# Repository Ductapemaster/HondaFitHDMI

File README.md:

# HondaFitHDMI
Various efforts into hacking the 2015 Honda Fit head unit to allow HDMI input and disable other lockouts while driving

A demonstration of the prototype hardware can be found here: http://youtu.be/ffWo1LNsV7A

Please see the Wiki for the most updated information!

## Contents
**./can_analysis**: Captured data from CAN bus.  Analysis spreadsheet showing various IDs and their functions

**./proof_of_concept**: Files relating to the proof of concept hardware and software

**./teensy**: Firmware and related information for teensy-based prototype hardware

**./wiki**: Wiki content

# Git-iquette
Please forgive my tresspasses on the typical Git workflow.  This is my first solo git-tracked project and I'm learning as I go along!

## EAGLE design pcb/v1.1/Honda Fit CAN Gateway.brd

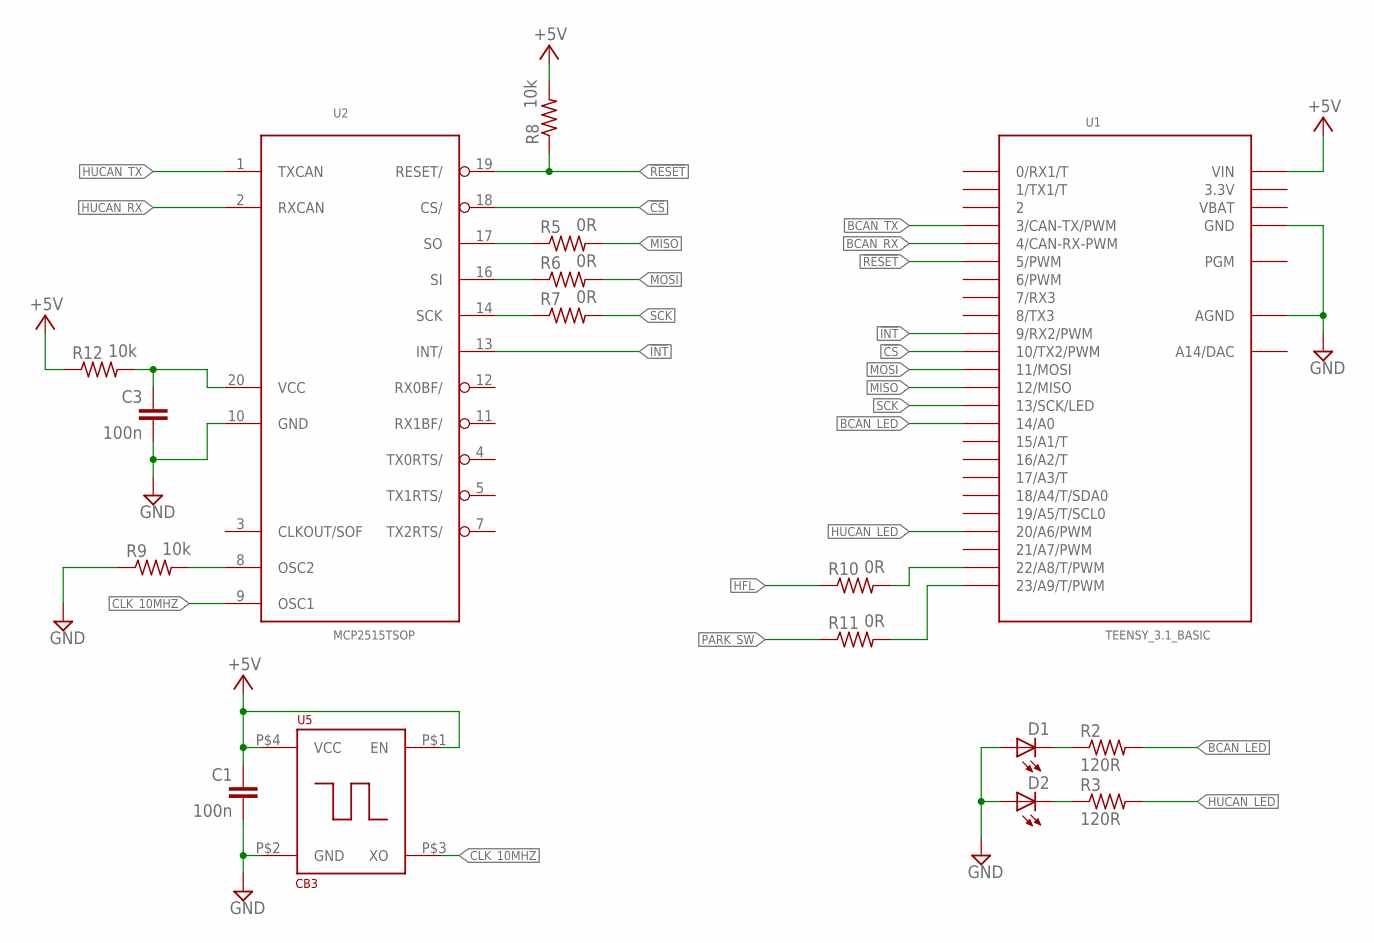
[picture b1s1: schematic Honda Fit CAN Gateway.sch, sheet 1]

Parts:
C1, C3: 100n; C0603
D1, D2: LEDCHIP-LED0805; CHIP-LED0805
R2, R3: 120R; R0805
R5, R6, R7, R10, R11: 0R; R0805
R8, R9, R12: 10k; R0805
U1: TEENSY_3.1_BASIC
U2: MCP2515TSOP; TSSOP20
U5: CB3; 4-SMD

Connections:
3.3V: U1.3.3V, U1.3.3V1 (3.3V)
!CS: U1.10 (10/TX2/PWM), U2.18 (CS/)
!INT: U1.9 (9/RX2/PWM), U2.13 (INT/)
!RESET: R8.1, U1.5 (5/PWM), U2.19 (RESET/)
+5V: C1.1, R8.2, R12.1, U1.VIN, U5.P$1 (EN), U5.P$4 (VCC); also elsewhere on the board
BCAN_LED: R2.2, U1.14/A0
BCAN_RX: U1.4 (4/CAN-RX-PWM); also elsewhere on the board
BCAN_TX: U1.3 (3/CAN-TX/PWM); also elsewhere on the board
CLK_10MHZ: U2.9 (OSC1), U5.P$3 (XO)
GND: C1.2, C3.2, D1.A, D2.A, R9.1, U1.AGND, U1.GND, U1.GND1 (GND), U2.10 (GND), U5.P$2 (GND); also elsewhere on the board
HFL: R10.1; also elsewhere on the board
HUCAN_LED: R3.2, U1.20/A6 (20/A6/PWM)
HUCAN_RX: U2.2 (RXCAN); also elsewhere on the board
HUCAN_TX: U2.1 (TXCAN); also elsewhere on the board
MISO: R5.2, U1.12 (12/MISO)
MOSI: R6.2, U1.11 (11/MOSI)
unnamed: R9.2, U2.8 (OSC2)
unnamed: R10.2, U1.22/A8 (22/A8/T/PWM)
unnamed: R11.2, U1.23/A9 (23/A9/T/PWM)
unnamed: D1.C, R2.1
unnamed: D2.C, R3.1
unnamed: R5.1, U2.17 (SO)
unnamed: R6.1, U2.16 (SI)
unnamed: R7.1, U2.14 (SCK)
unnamed: C3.1, R12.2, U2.20 (VCC)
PARK_SW: R11.1; also elsewhere on the board
SCK: R7.2, U1.13 (13/SCK/LED)
VBAT: U1.VBAT

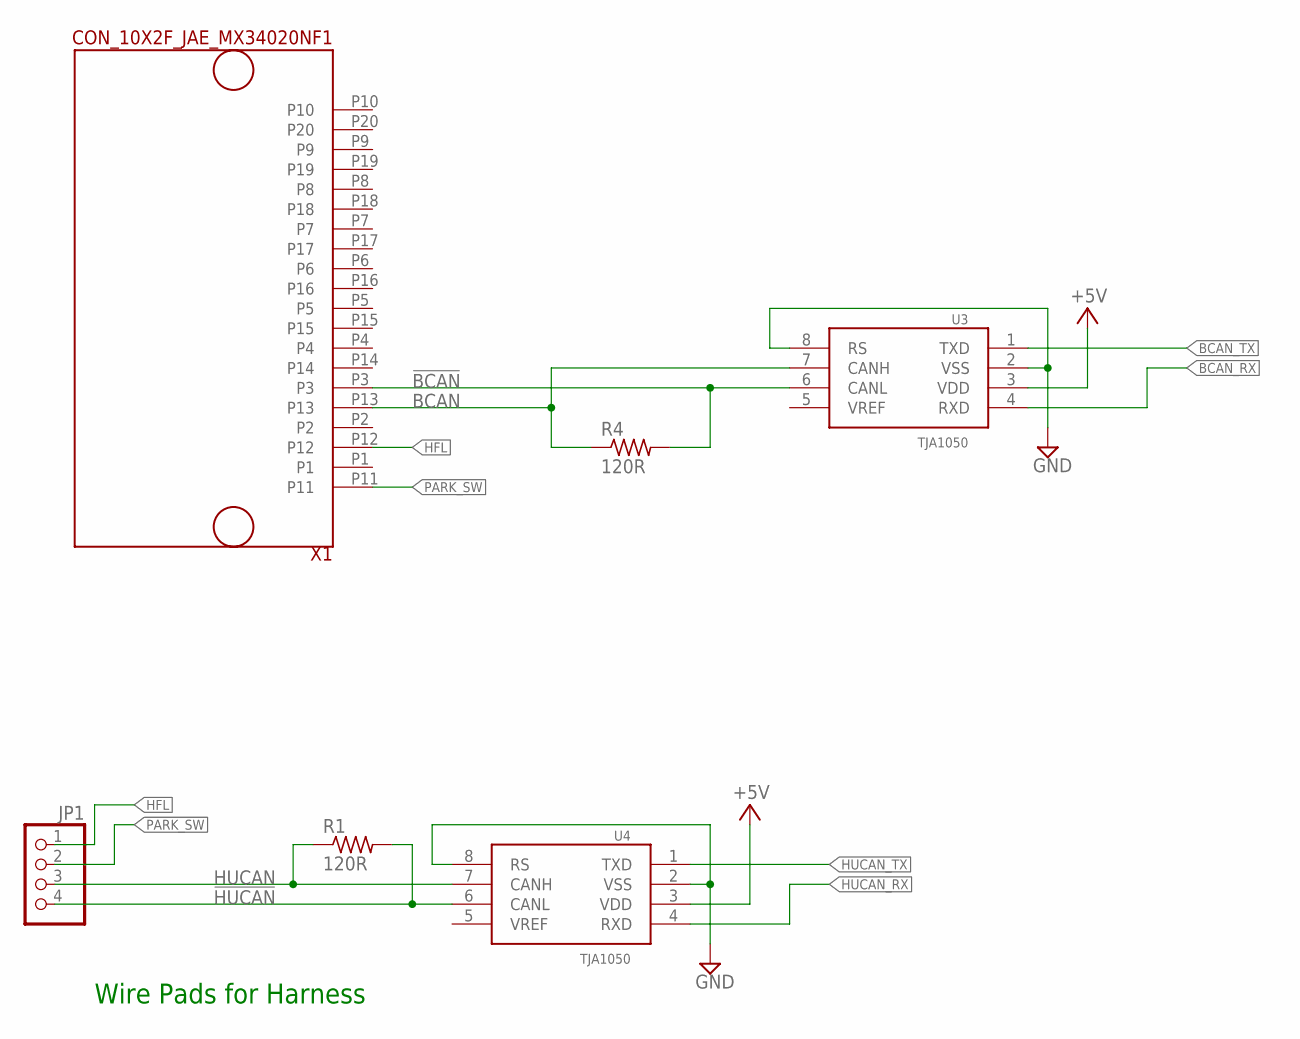
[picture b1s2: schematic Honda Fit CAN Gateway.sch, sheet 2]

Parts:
JP1: PINHD-1X4; 1X04
R1, R4: 120R; R0805
U3, U4: TJA1050; SO08
X1: CON_10X2F_JAE_MX34020NF1; CON_10X2_JAE_MX34020NF1

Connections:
!BCAN: R4.2, U3.6 (CANL), X1.P3
!HUCAN: JP1.4, R1.2, U4.6 (CANL)
+5V: U3.3 (VDD), U4.3 (VDD); also elsewhere on the board
BCAN: R4.1, U3.7 (CANH), X1.P13
BCAN_RX: U3.4 (RXD); also elsewhere on the board
BCAN_TX: U3.1 (TXD); also elsewhere on the board
GND: U3.2 (VSS), U3.8 (RS), U4.2 (VSS), U4.8 (RS); also elsewhere on the board
HFL: JP1.1, X1.P12; also elsewhere on the board
HUCAN: JP1.3, R1.1, U4.7 (CANH)
HUCAN_RX: U4.4 (RXD); also elsewhere on the board
HUCAN_TX: U4.1 (TXD); also elsewhere on the board
PARK_SW: JP1.2, X1.P11; also elsewhere on the board

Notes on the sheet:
Wire Pads for Harness

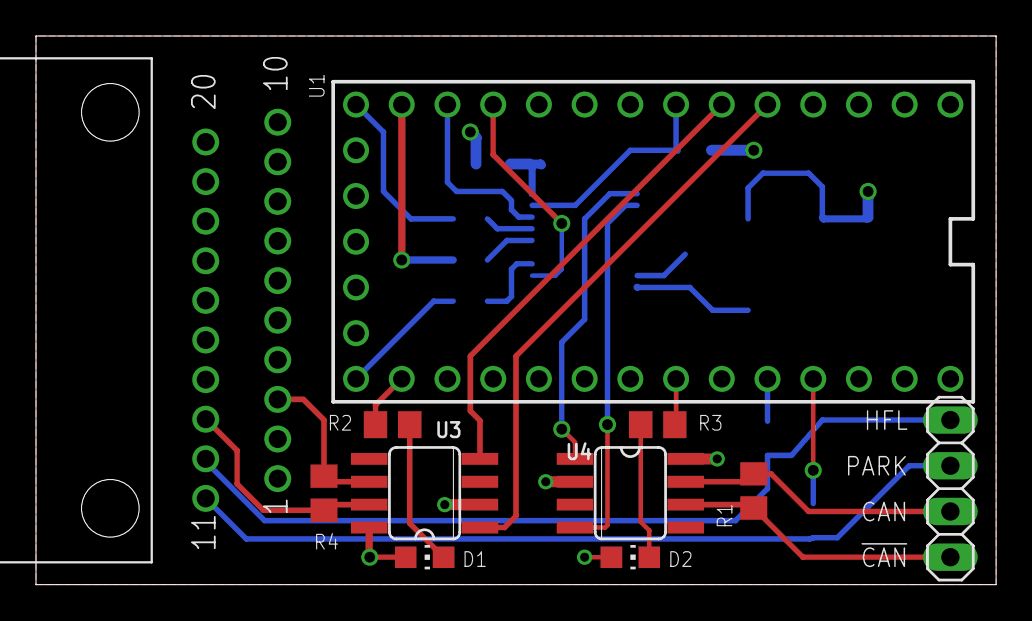
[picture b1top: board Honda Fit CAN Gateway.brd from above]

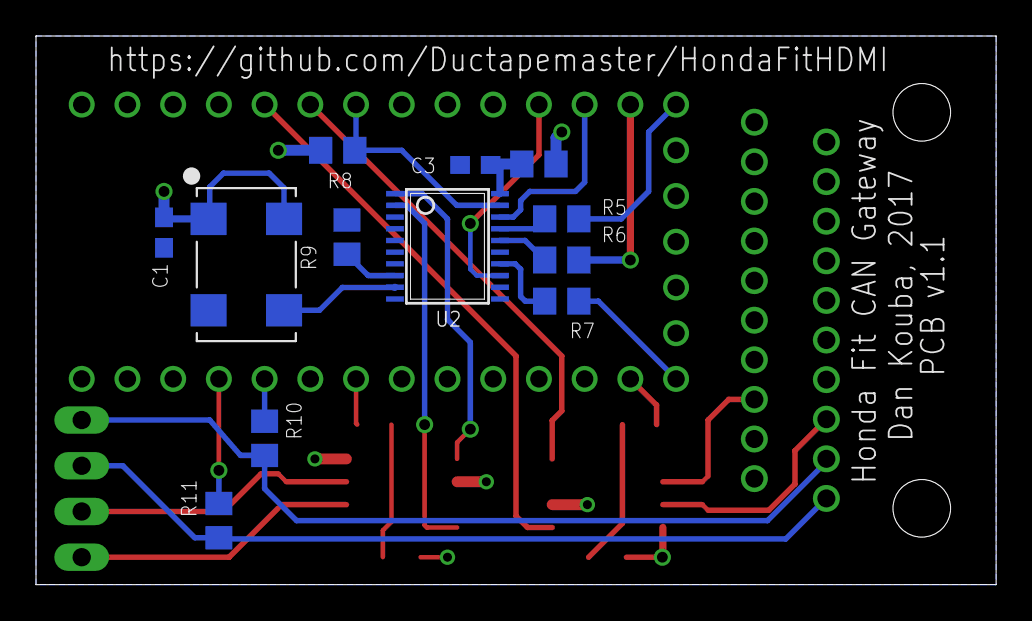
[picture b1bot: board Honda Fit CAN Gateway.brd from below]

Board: 2 copper layers, 53.3 x 30.5 mm, 23 parts (12 on the bottom side), 31 nets.

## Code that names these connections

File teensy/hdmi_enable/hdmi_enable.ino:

// -------------------------------------------------------------
// hdmi_enable for Teensy 3.1
// by ductapemaster
//
// This code successfully disables HDMI lockout and lockout of specific features at speed.
//
// Two frames are edited before passing through:
// 1. Gear shifter value set permanently to "park"
// 2. Vehicle speed value set permanently to '0'
//
// Only passes CAN data from car to head unit.  Head unit output frames are currently unhandled.

#include <FlexCAN.h>
#include <teensy_mcp_can.h>
#include<SPI.h>
#include <spi4teensy3.h>

//#define debug

// LED for receive indication.  Can't use onboard one because it shares the SPI SCLK pin
const int bcan_led  = 14;
const int hucan_led = 20;
const int park      = 22;
const int hfl       = 23;
const int rst       = 5;

//FlexCAN
FlexCAN CANIn(125000);
static CAN_message_t rxmsg;

//MCP2515 CAN
//Interrupt is D2, from schematic
//Default SPI Pins on Teensy:
// CS:        10
// DOUT/MOSI: 11
// DIN/MISO   12
// SCLK       13 (also the LED!)

//MCP library requires CS pin as argument.  Use default.
// this actually doesn't matter since we are overwriting the calls to the Arduino SPI lib with calls to spi4teensy3
const int csPin = 10;
MCP_CAN CANOut(csPin);
bool filter_out = false;

// -------------------------------------------------------------
static void printCanFrame(CAN_message_t f)
{
      Serial.print(millis());
      Serial.print("ms");
      Serial.print("\t0x");
      Serial.print(f.id, HEX);
      Serial.print("\t[");
      Serial.print(f.len);
      Serial.print("]\t");
      for (int i = 0; i < f.len; i++) 
      {
        Serial.print(f.buf[i], HEX);
        Serial.print("  ");
      }
      Serial.write('\r');
      Serial.write('\n');
}

// -------------------------------------------------------------
void setup(void)
{

  CANIn.begin();
  Serial.begin(115200);

  // MCP2515 Reset Setup
  pinMode(rst, OUTPUT);
  digitalWrite(rst, 0);

  // LED Setup
  pinMode(bcan_led,  OUTPUT);
  pinMode(hucan_led, OUTPUT);
  digitalWrite(bcan_led,  0);
  digitalWrite(hucan_led, 0);

  // Inputs
  pinMode(park, INPUT);
  pinMode(hfl,  INPUT);

  delay(1000);

  // Bring MCP2515 out of reset
  digitalWrite(rst, 1);
  
  // F() stores string in flash rather than RAM
  Serial.println(F("HDMI Enable Test"));

  Serial.print(F("Initializing MCP2515 interface..."));

  // Attempt to initialize module
  while (CAN_OK != CANOut.begin(CAN_125KBPS))
  {
    // Loops forever - probably should implement some sort of timeout.  Watchdog?
    Serial.print(".");
    delay(300);
  }
  
  Serial.println("success\r\n");

  digitalWrite(bcan_led, 1);
  digitalWrite(hucan_led, 1);

}


// -------------------------------------------------------------
void loop(void)
{
    // Poll CAN buffer for new data
    while ( CANIn.read(rxmsg) ) {

      filter_out = false;

      // Toggle our LED to show bus activity
      digitalWrite(bcan_led, 1);
      
      #ifdef debug
      printCanFrame(rxmsg);
      #endif

      // Modify multiple frames based on conditional data
      switch (rxmsg.id) {

        // Gear Shifter/Parking Brake Position
        case 0x12F85150:
          
          Serial.println("changing gear to park!");
          Serial.print("before: ");
          printCanFrame(rxmsg);
          rxmsg.buf[0] = 0x40;
          rxmsg.buf[1] = 0x03;
          Serial.print("after: ");
          printCanFrame(rxmsg);
          break;

        // Vehicle Speed/Engine RPM - verified!
        case 0x12F85050:
          Serial.println("changing speed to 0!!");
          Serial.print("before: ");
          printCanFrame(rxmsg);
          rxmsg.buf[0] = 0x00;
          Serial.print("after: ");
          printCanFrame(rxmsg);
          break;        
          
        default:
          break;
        
      }
      
      digitalWrite(bcan_led, 0);

      // Write buffered data to second CAN bus
      // ID, CAN Mode: 1=extended, buffer length, buffer     
      // There's got to be a better way to do this - can we use the canframe object?
      //if (!filter_out)
      //{
        digitalWrite(hucan_led, 1);
        CANOut.sendMsgBuf(rxmsg.id, 1, rxmsg.len, rxmsg.buf);
        digitalWrite(hucan_led, 0);
      //}
      
    }

    

}

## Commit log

2015-08-04 Initial commit. Incudes 4 caputres of data from the B-CAN network in the car and the beginnings of a parser program.
2015-08-04 Script actually works now! Parses can data into a list of canframe objects.
2015-08-04 Playing around with the parser. Prints out some debug info now, and also a list of unique addresses and how many frames occured with that specific address
2015-08-05 Various functions added to parser. Creates CSV for input file and outputs interesting addresses. CSV files committed. Forked c library for reading CAN data live from interface for future monitoring p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
2015-08-05 Refactored the entropy function to be more generic. Renamed some variables.
2015-08-05 adding capture of shifter ID only from today
2015-08-06 Adding some new log files from an actual drive. Got the toyothack code working with some of the decoded Honda CAN IDs. Discovered the turn signal ID.
2015-08-09 Genericizing parser program further.
2015-08-09 Renaming files
2015-08-09 updating canhack submodule
2015-08-09 commits to submodule
2015-08-09 Added script that sends out CAN frame repeatedly representing the car being in park. This partially triggers the desired behavior of the head unit - the correct video enabled flags are set in the dia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
2015-08-10 updating canhack
2015-08-10 fixing reference error
2015-08-15 Adding directory for wiki content. Adding prototype block diagram
2015-08-15 Block diagram updates. Adding HTML source.
2015-08-20 Adding head unit disassembly pics and datasheets for parts.
2015-08-20 moving things around
2015-08-22 Removing canhack subproject. Adding teensy tests for prototype hardware.
2015-08-22 Adding working prototype code. Successfully passes through CAN data to head unit and modifying gear shifter frame to be in park, which enables HDMI input all the time.
2015-08-22 Updating readme with link to demonstration video
2015-08-27 Cleaning things up and adding CAN bus analysis spreadsheet
2015-08-27 Readability fixes in CAN bus analysis spreadsheet
2015-08-28 Consolidating teensy firmware files. Adding working version of code for enabling HDMI and other locked out features while driving
2015-08-28 Cleaning up more firmware files
2015-08-28 Updating readme
2015-08-28 Adding part libraries
2015-08-31 Two-way CAN communication enabled. Serial output formatting is customizeable now
2015-09-03 Consolidating firmware features into one file. Added rudimentary serial interface for monitoring.
2015-09-03 Renaming ino file to fix IDE errors
2015-11-02 Adding schematic and pcb files. v1.0 was sent to fab
2015-11-02 Creating v1.1 schematic and pcb files from v1.0
2017-01-24 Add gitignore
2017-01-24 Add series resistors on MCP2515 SPI lines
    Lands can be used for any 0603 part
2017-01-24 Add Eagle library with tiny Kemet relay
    For future versions
2017-01-24 Add datasheet for 1.2A buck converter
    For future designs
2017-01-24 Add 10k pullup for reset
    Datasheet recommended
2017-01-24 Replace xtal with oscillator. Connect reset to Teensy
2017-01-24 Replace discrete pads for output with pin header footprint
    Pads were too large on rev 1, and square orientation was not ideal
2017-01-26 Major additions and changes
    Added jumper resistors between Park and HFL nets and the Teensy to allow decoupling. Added land for inductor on MCP2515 +5V rail (805 resistor package). Reordered some pins to make layout easier.
2017-01-26 V1.1 PCB preliminary commit
    Need to review. All signals routed - no rats.
2017-01-26 Change resistor value
    Change resistor land used for MCP2515 supply inductor to be 0 ohms for clarity
2017-01-31 Move silkscreen and a couple of traces
2017-01-31 Add datasheet for JAE MX34 connector
2017-04-10 Remove eagle project files
2017-04-10 Add newest teensy firmware files
2017-04-10 Update README.md
    Fix markdown
2017-04-10 Update README.md
    More markdown fixes
2017-04-10 Add v1.1 pcb files for starting point
